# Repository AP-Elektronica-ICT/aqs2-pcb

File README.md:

# Schema airsensor

# Schema LoRaWAN

# Schema HIH8xxx

# Schema JTAG
<<<<<<< HEAD

=======

>>>>>>> c74764702c0ad45f76e91693a2fbca707ce8f4d9

# PCB airsensor

# PCB LoRaWAN

# PCB HIH8xxx

# PCB JTAG
<<<<<<< HEAD

=======

>>>>>>> c74764702c0ad45f76e91693a2fbca707ce8f4d9

# 3D airsensor

# 3D LoRaWAN

# 3D HIH8xxx

# 3D JTAG
<<<<<<< HEAD

=======

>>>>>>> c74764702c0ad45f76e91693a2fbca707ce8f4d9

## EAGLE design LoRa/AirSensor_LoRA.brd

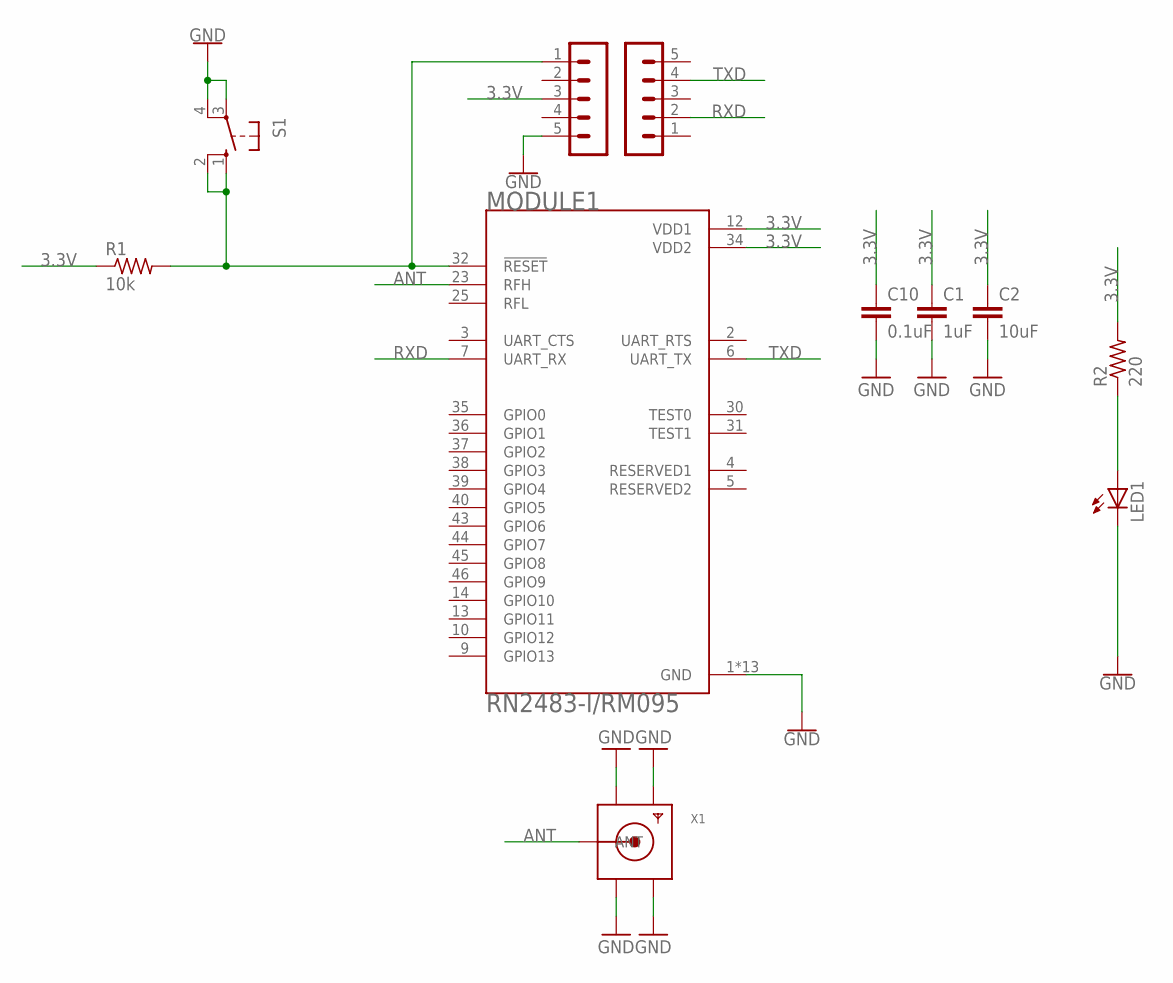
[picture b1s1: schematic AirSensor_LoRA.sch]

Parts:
C1: 1uF; 0805
C2: 10uF; 0805
C10: 0.1uF; 0805
LED1: LEDCHIPLED_0805; CHIPLED_0805
MODULE1: RN2483-I/RM095; MICROCHIP_RN2483-I/RM095
R1: 10k; RES_0805
R2: 220; RES_0805
RFM95W_1: LoRa_1; MA05-1
RFM95W_2: LoRa_2; MA05-1
S1: 10-XX; B3F-10XX
X1: SMACONNECTOR_EDGE; SMA_EDGELAUNCH

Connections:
3.3V: C1.1, C2.1, C10.1, MODULE1.12 (VDD1), MODULE1.34 (VDD2), R1.1, R2.2, RFM95W_1.3
ANT: MODULE1.23 (RFH), X1.P (ANT)
GND: C1.2, C2.2, C10.2, LED1.C, MODULE1.1 (GND), MODULE1.8 (GND), MODULE1.11 (GND), MODULE1.20 (GND), MODULE1.21 (GND), MODULE1.22 (GND), MODULE1.24 (GND), MODULE1.26 (GND), MODULE1.27 (GND), MODULE1.28 (GND), MODULE1.33 (GND), MODULE1.41 (GND), MODULE1.47 (GND), RFM95W_1.5, S1.3, S1.4 (P1), X1.GND@1 (GND4), X1.GND@2 (GND3), X1.GND@3 (GND2), X1.GND@4 (GND1)
unnamed: LED1.A, R2.1
unnamed: MODULE1.32 (!RESET), R1.2, RFM95W_1.1, S1.1 (S), S1.2 (S1)
RXD: MODULE1.7 (UART_RX), RFM95W_2.2
TXD: MODULE1.6 (UART_TX), RFM95W_2.4

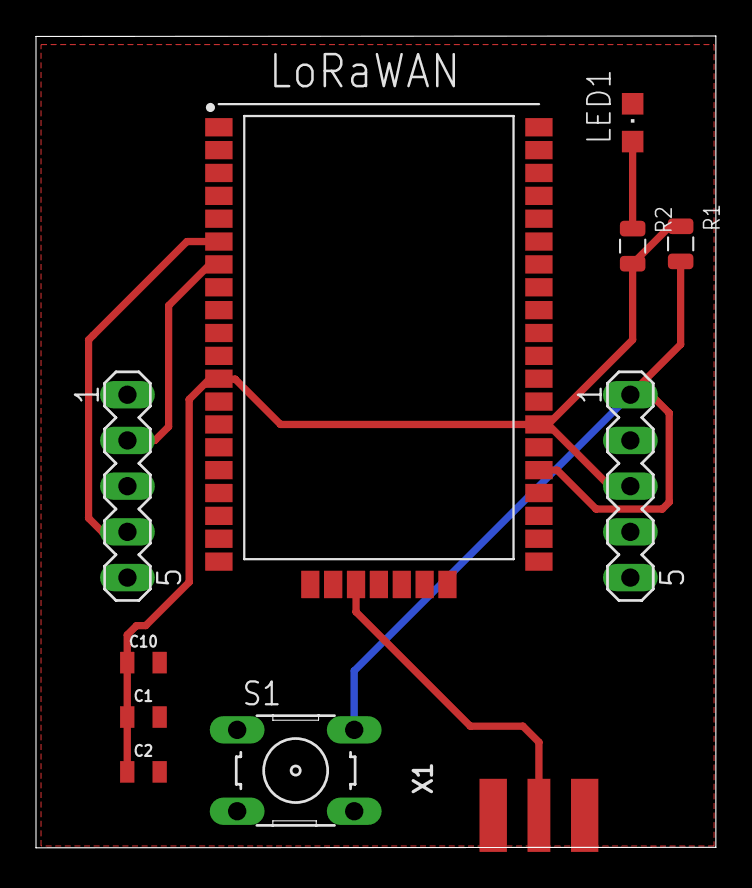
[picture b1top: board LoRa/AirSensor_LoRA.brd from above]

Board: 2 copper layers, 37.8 x 45.1 mm, 11 parts (0 on the bottom side), 7 nets.

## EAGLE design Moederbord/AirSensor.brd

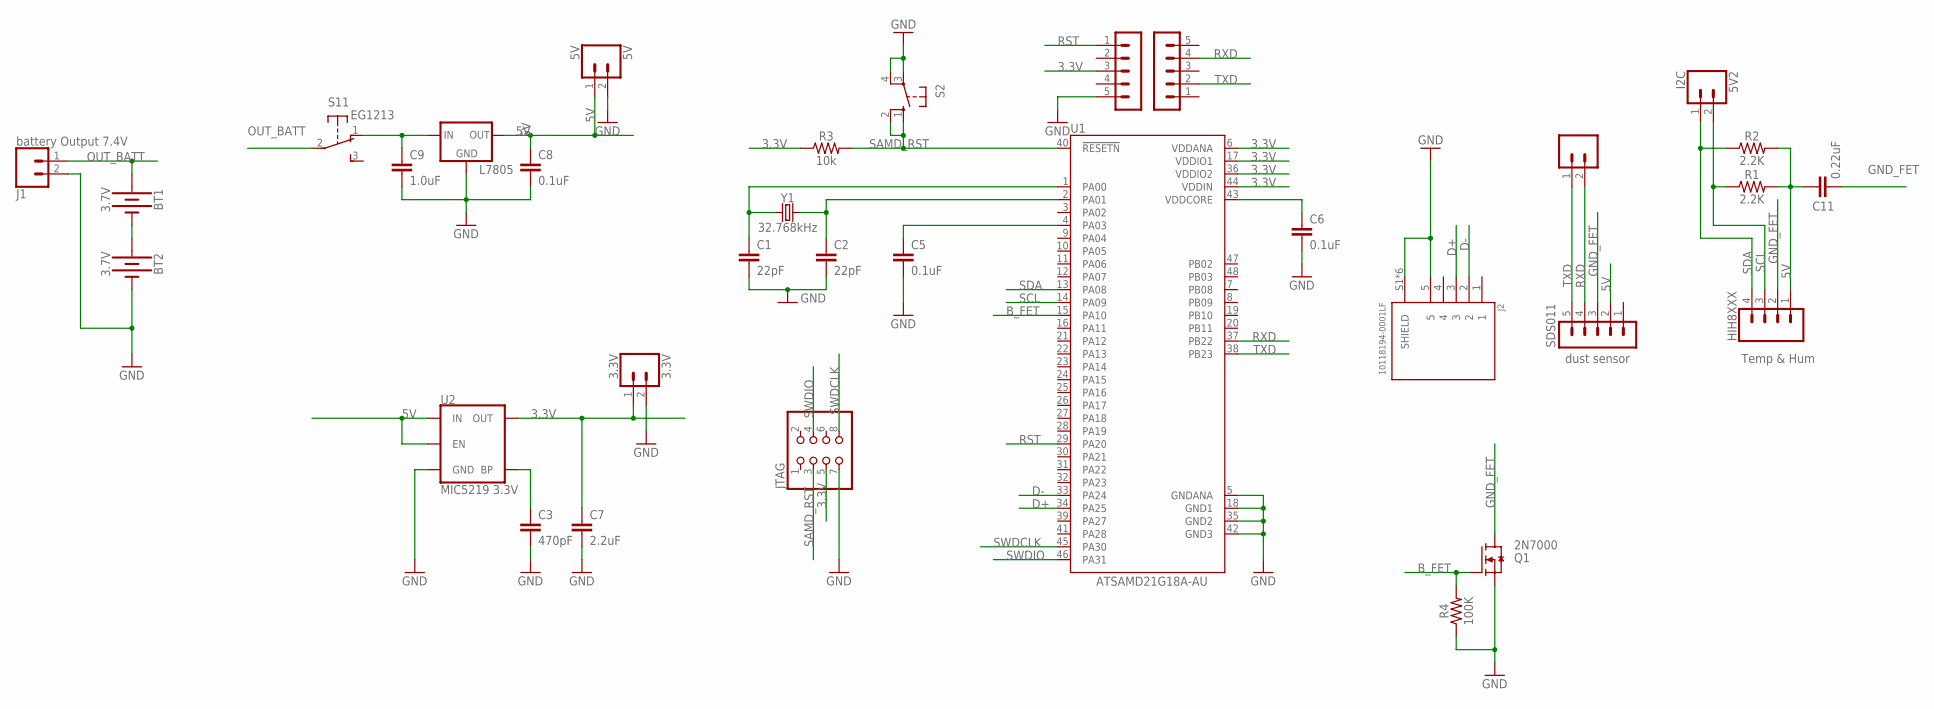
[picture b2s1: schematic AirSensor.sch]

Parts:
3.3V: 3.3V; 1X02
5V: 5V; 1X02
5V1: UART; 1X02
5V2: I2C; 1X02
BT1, BT2: 3.7V; BATTERY_18650-HOLDER
C1, C2: 22pF; 0805
C3: 470pF; 0805
C5, C6, C8: 0.1uF; 0805
C7: 2.2uF; 0805
C9: 1.0uF; 0805
C11: 0.22uF; 0805
HIH8XXX: Temp & Hum; 1X04
J1: battery Output 7.4V; 1X02
J2: 10118194-0001LF; AMPHENOL_10118194-0001LF
JTAG: PINHD-2X4; 2X04
L7805: V_REG_78XXSINK; TO220-IGO
Q1: 2N7000; TO92
R1, R2: 2.2K; 0805
R3: 10k; 0805
R4: 100K; 0805
RN2483: LoRa1; MA05-1
RN2483_2: LoRa_2; MA05-1
S1: EG1213
S2: 10-XX; B3F-10XX
SDS011: dust sensor; MA05-1
U1: ATSAMD21G18A-AU; QFP50P900X900X120-48N
U2: MIC5219 3.3V; SOT23-5
Y1: 32.768kHz; CRYSTAL-SMD-3.2X1.5MM

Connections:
3.3V: 3.3V.1, C7.1, JTAG.5, R3.1, RN2483.3, U1.6 (VDDANA), U1.17 (VDDIO1), U1.36 (VDDIO2), U1.44 (VDDIN), U2.5 (OUT)
5V: 5V.1, C8.1, C11.1, HIH8XXX.1, L7805.OUT, R1.2, R2.2, SDS011.2, U2.1 (IN), U2.3 (EN)
B_FET: Q1.2 (G), R4.2, U1.15 (PA10)
D+: J2.3, U1.34 (PA25)
D-: J2.2, U1.33 (PA24)
GND: 3.3V.2, 5V.2, BT2.GND@1 (-), C1.2, C2.2, C3.2, C5.2, C6.2, C7.2, C8.2, C9.2, J1.2, J2.5, J2.S1 (SHIELD), J2.S2 (SHIELD), J2.S3 (SHIELD), J2.S4 (SHIELD), J2.S5 (SHIELD), J2.S6 (SHIELD), JTAG.7, L7805.GND, Q1.1 (S), R4.1, RN2483.5, S2.3, S2.4 (P1), U1.5 (GNDANA), U1.18 (GND1), U1.35 (GND2), U1.42 (GND3), U2.2 (GND)
GND_FET: C11.2, HIH8XXX.2, Q1.3 (D), SDS011.3
unnamed: C5.1, U1.4 (PA03)
unnamed: C6.1, U1.43 (VDDCORE)
unnamed: C1.1, U1.1 (PA00), Y1.P$1 (1)
unnamed: C3.1, U2.4 (BP)
unnamed: BT1.GND@1 (-), BT2.PWR@1 (+)
unnamed: C2.1, U1.2 (PA01), Y1.P$2 (2)
OUT_BATT: BT1.PWR@1 (+), C9.1, J1.1, L7805.IN, S1.1 (O), S1.2
RST: RN2483.1, U1.29 (PA20)
RXD: 5V1.2, RN2483_2.4, SDS011.4, U1.37 (PB22)
SAMD_RST: JTAG.3, R3.2, S2.1 (S), S2.2 (S1), U1.40 (!RESETN)
SCL: 5V2.2, HIH8XXX.3, R1.1, U1.14 (PA09)
SDA: 5V2.1, HIH8XXX.4, R2.1, U1.13 (PA08)
SWDCLK: JTAG.8, U1.45 (PA30)
SWDIO: JTAG.4, U1.46 (PA31)
TXD: 5V1.1, RN2483_2.2, SDS011.5, U1.38 (PB23)

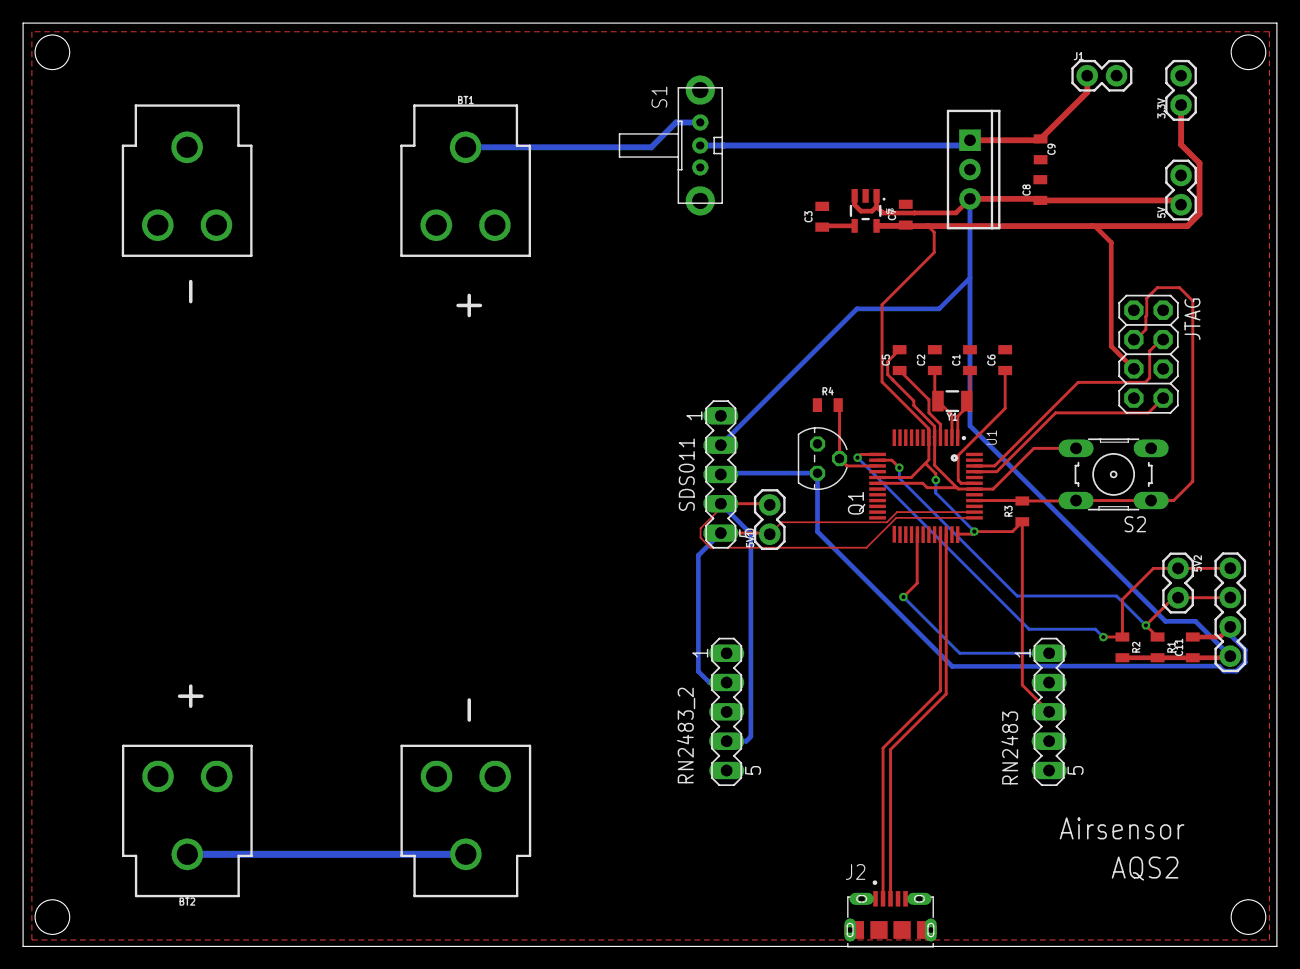
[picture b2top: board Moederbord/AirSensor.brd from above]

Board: 2 copper layers, 108.6 x 80.0 mm, 33 parts (0 on the bottom side), 22 nets.

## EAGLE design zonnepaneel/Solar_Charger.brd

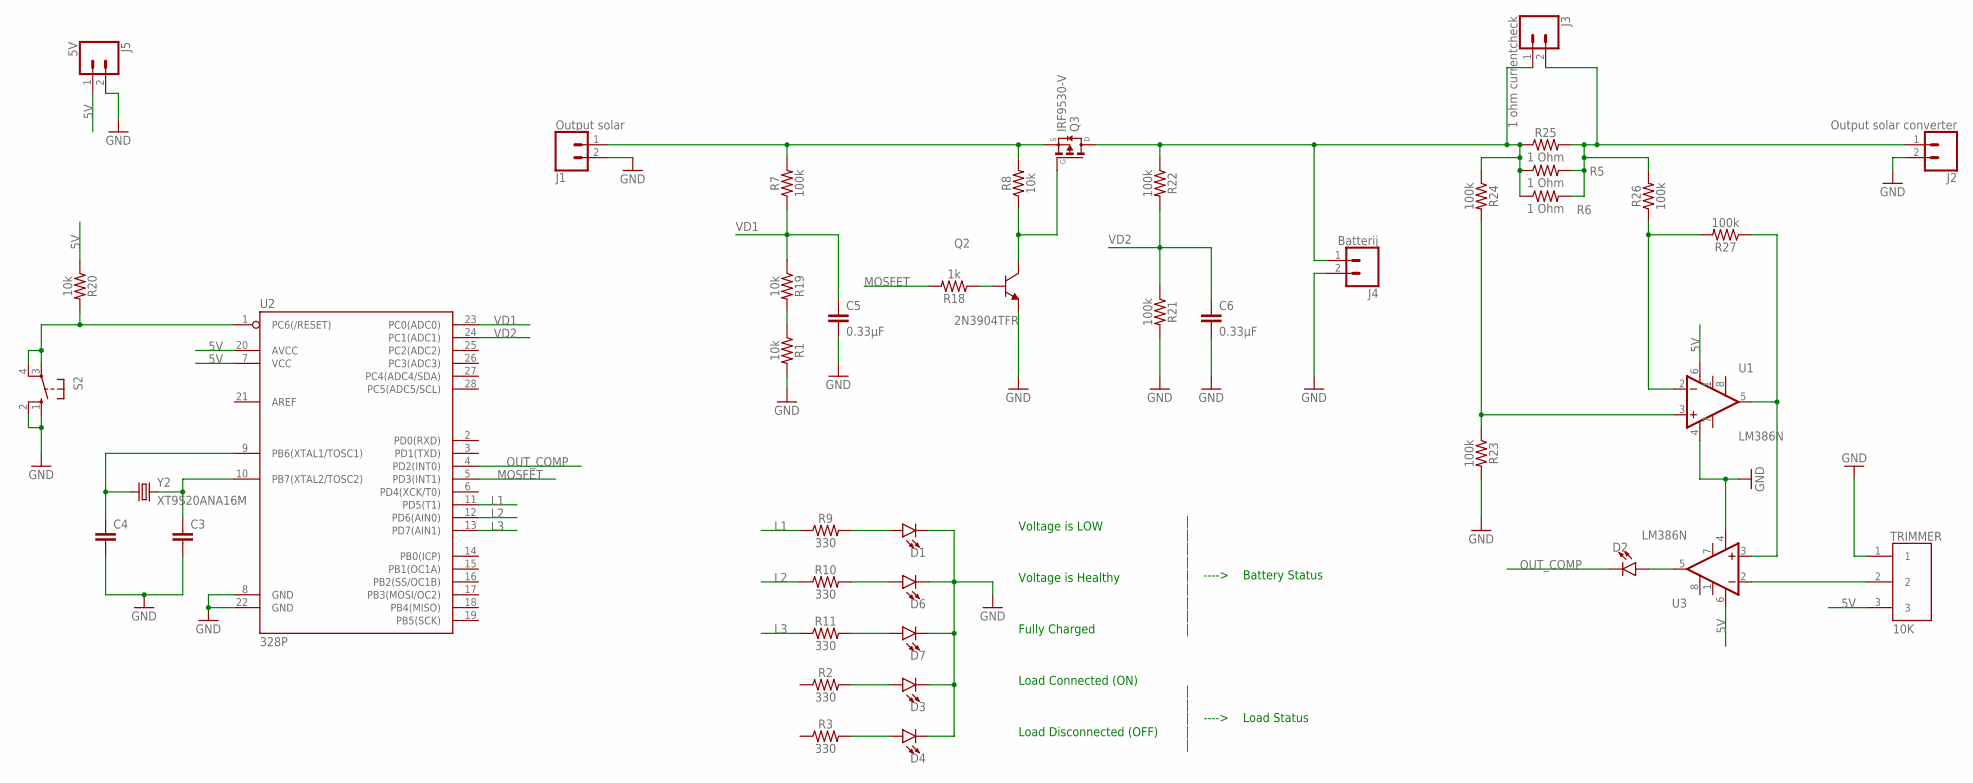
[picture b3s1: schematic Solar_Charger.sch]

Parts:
C3, C4: C2.5/5; C2.5-5
C5, C6: 0.33µF; C2.5-5
D1, D2, D3, D4, D6, D7: LED-3MM-NO_SILK; LED_3MM-NS
J1: Output solar; 1X02
J2: Output solar converter; 1X02
J3: 1 ohm currentcheck; 1X02
J4: Batterij; 1X02
J5: 5V; 1X02
Q2: 2N3904TFR; TO92254P520H877-3
Q3: IRF9530-V; TO220V
R1, R8, R19, R20: 10k; AXIAL-0.3
R2, R3, R9, R10, R11: 330; AXIAL-0.3
R5, R6, R25: 1 Ohm; AXIAL-0.3
R7, R21, R22, R23, R24, R26, R27: 100k; AXIAL-0.3
R18: 1k; AXIAL-0.3
S2: 10-XX; B3F-10XX
TRIMMER: 10K; TRIM_404806347006
U1, U3: LM386N; DIP08
U2: 328P; DIP28
Y2: XT9S20ANA16M; XTAL_XT9S20ANA16M

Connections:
5V: J5.1, R20.P$1 (1), TRIMMER.3, U1.6 (V+), U2.7 (VCC), U2.20 (AVCC), U3.6 (V+)
GND: C3.2, C4.2, C5.2, C6.2, D1.K (C), D3.K (C), D4.K (C), D6.K (C), D7.K (C), J1.2, J2.2, J4.2, J5.2, Q2.1 (E), R1.P$2 (2), R21.P$2 (2), R23.P$2 (2), S2.1 (S), S2.2 (S1), TRIMMER.1, U1.4 (V-), U2.8 (GND), U2.22 (GND), U3.4 (V-)
GND1: R20.P$2 (2), S2.3, S2.4 (P1), U2.1 (PC6(/RESET))
L1: R9.P$1 (1), U2.11 (PD5(T1))
L2: R10.P$1 (1), U2.12 (PD6(AIN0))
L3: R11.P$1 (1), U2.13 (PD7(AIN1))
MOSFET: R18.P$2 (2), U2.5 (PD3(INT1))
unnamed: J1.1, Q3.3 (S), R7.P$2 (2), R8.P$2 (2)
unnamed: D3.A, R2.P$2 (2)
unnamed: D4.A, R3.P$2 (2)
unnamed: R23.P$1 (1), R24.P$2 (2), U1.3 (+IN)
unnamed: R26.P$1 (1), R27.P$2 (2), U1.2 (-IN)
unnamed: R1.P$1 (1), R19.P$2 (2)
unnamed: C4.1, U2.9 (PB6(XTAL1/TOSC1)), Y2.1
unnamed: C3.1, U2.10 (PB7(XTAL2/TOSC2)), Y2.2
unnamed: Q2.2 (B), R18.P$1 (1)
unnamed: Q2.3 (C), Q3.1 (G), R8.P$1 (1)
unnamed: J3.1, J4.1, Q3.2 (D), R5.P$1 (1), R6.P$1 (1), R22.P$1 (1), R24.P$1 (1), R25.P$1 (1)
unnamed: R27.P$1 (1), U1.5 (OUT), U3.3 (+IN)
unnamed: TRIMMER.2, U3.2 (-IN)
unnamed: D2.A, U3.5 (OUT)
unnamed: J2.1, J3.2, R5.P$2 (2), R6.P$2 (2), R25.P$2 (2), R26.P$2 (2)
unnamed: D1.A, R9.P$2 (2)
unnamed: D6.A, R10.P$2 (2)
unnamed: D7.A, R11.P$2 (2)
OUT_COMP: D2.K (C), U2.4 (PD2(INT0))
VD1: C5.1, R7.P$1 (1), R19.P$1 (1), U2.23 (PC0(ADC0))
VD2: C6.1, R21.P$1 (1), R22.P$2 (2), U2.24 (PC1(ADC1))

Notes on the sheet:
Voltage is LOW
Voltage is Healthy
Fully Charged
Load Connected (ON)
Load Disconnected (OFF)
| | | | | ----> Battery Status | | | |
| | | ----> Load Status | |

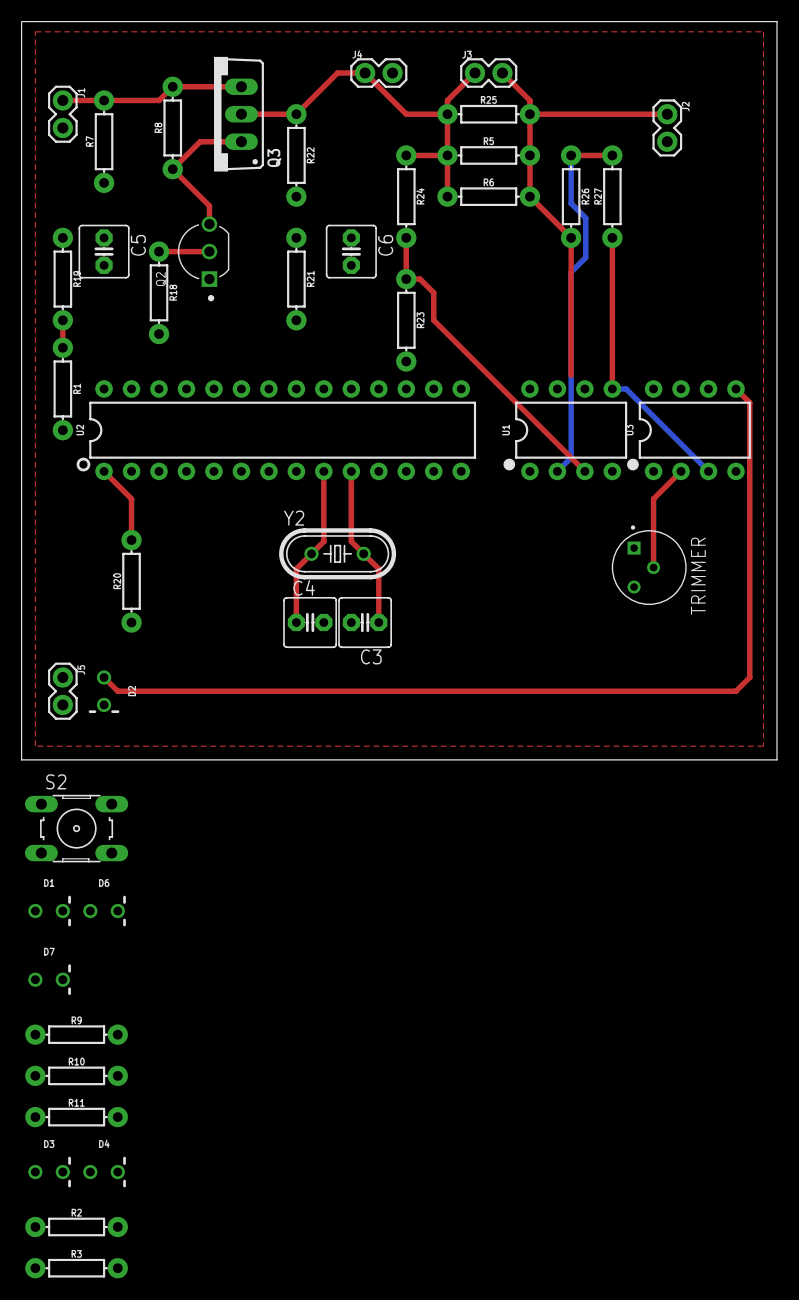
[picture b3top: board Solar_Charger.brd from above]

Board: 2 copper layers, 69.8 x 68.2 mm, 43 parts (0 on the bottom side), 28 nets.

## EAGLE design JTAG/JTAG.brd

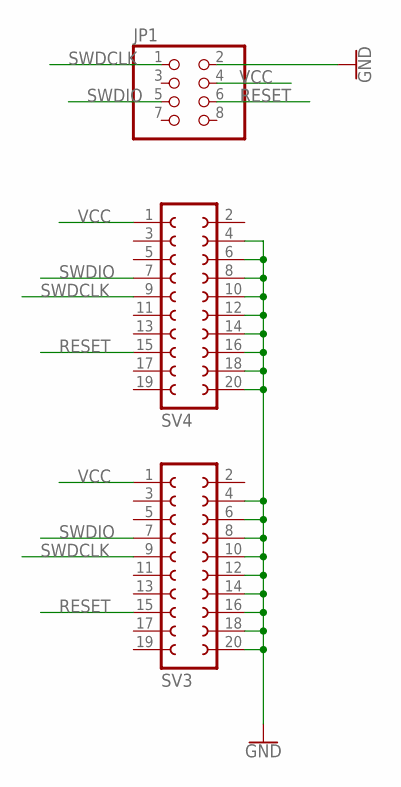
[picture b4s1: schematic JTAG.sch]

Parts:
JP1: PINHD-2X4; 2X04
SV3, SV4: FE10-2

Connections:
GND: JP1.2, SV3.4, SV3.6, SV3.8, SV3.10, SV3.12, SV3.14, SV3.16, SV3.18, SV3.20, SV4.4, SV4.6, SV4.8, SV4.10, SV4.12, SV4.14, SV4.16, SV4.18, SV4.20
RESET: JP1.6, SV3.15, SV4.15
SWDCLK: JP1.1, SV3.9, SV4.9
SWDIO: JP1.5, SV3.7, SV4.7
VCC: JP1.4, SV3.1, SV4.1

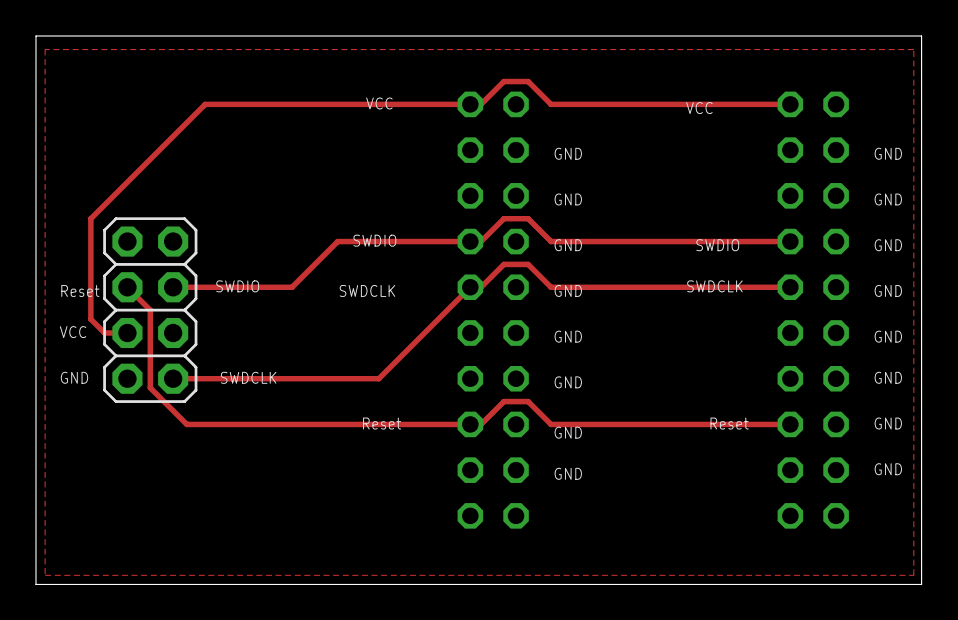
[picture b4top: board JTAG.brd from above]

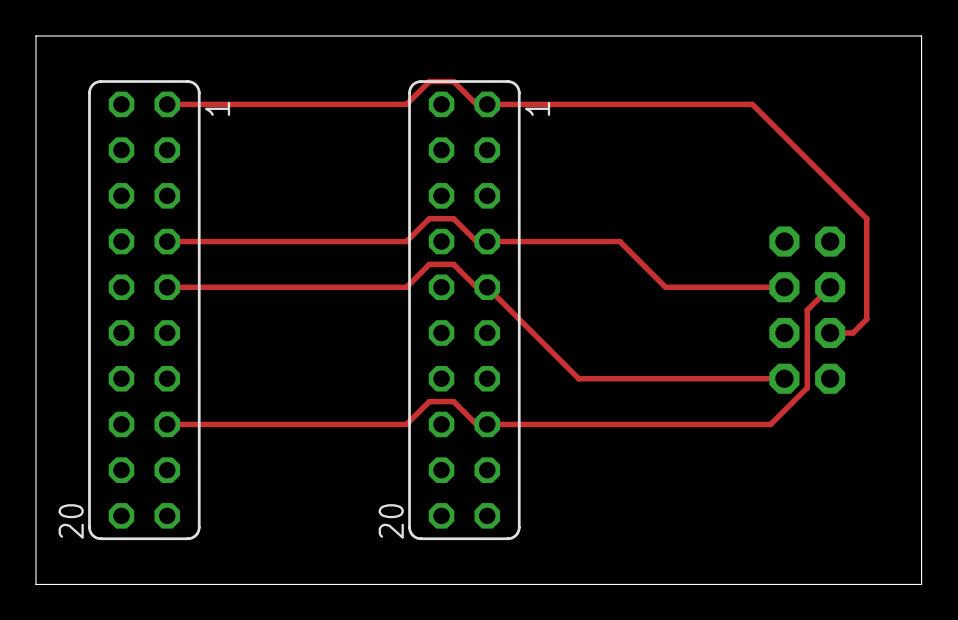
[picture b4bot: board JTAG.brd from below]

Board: 2 copper layers, 49.2 x 30.5 mm, 3 parts (2 on the bottom side), 5 nets.

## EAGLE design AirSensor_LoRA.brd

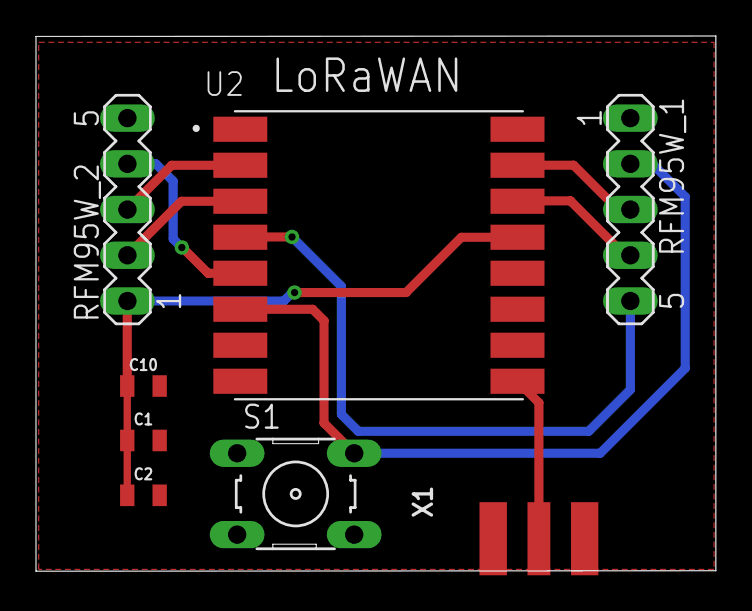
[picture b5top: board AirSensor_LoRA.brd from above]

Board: 2 copper layers, 37.8 x 29.7 mm, 8 parts (0 on the bottom side), 11 nets.

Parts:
C1: 1uF; 0805
C2: 10uF; 0805
C10: 0.1uF; 0805
RFM95W_1: LoRa_1; MA05-1
RFM95W_2: LoRa_2; MA05-1
S1: B3F-10XX
U2: RFM95W-915S2; XCVR_RFM95W-915S2
X1: SMA_EDGELAUNCH

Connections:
3.3V: S1.3, S1.4
GND: C1.2, C2.2, C10.2, RFM95W_2.5, U2.1, U2.8, U2.10, X1.GND@1, X1.GND@2, X1.GND@3, X1.GND@4
unnamed: RFM95W_1.2, S1.1, S1.2, U2.6
unnamed: C1.1, C2.1, C10.1, RFM95W_2.1, U2.13
unnamed: RFM95W_2.2, U2.3
unnamed: RFM95W_2.3, U2.2
unnamed: RFM95W_2.4, U2.5
unnamed: RFM95W_1.5, U2.4
unnamed: RFM95W_1.4, U2.14
unnamed: RFM95W_1.3, U2.15
unnamed: U2.9, X1.P

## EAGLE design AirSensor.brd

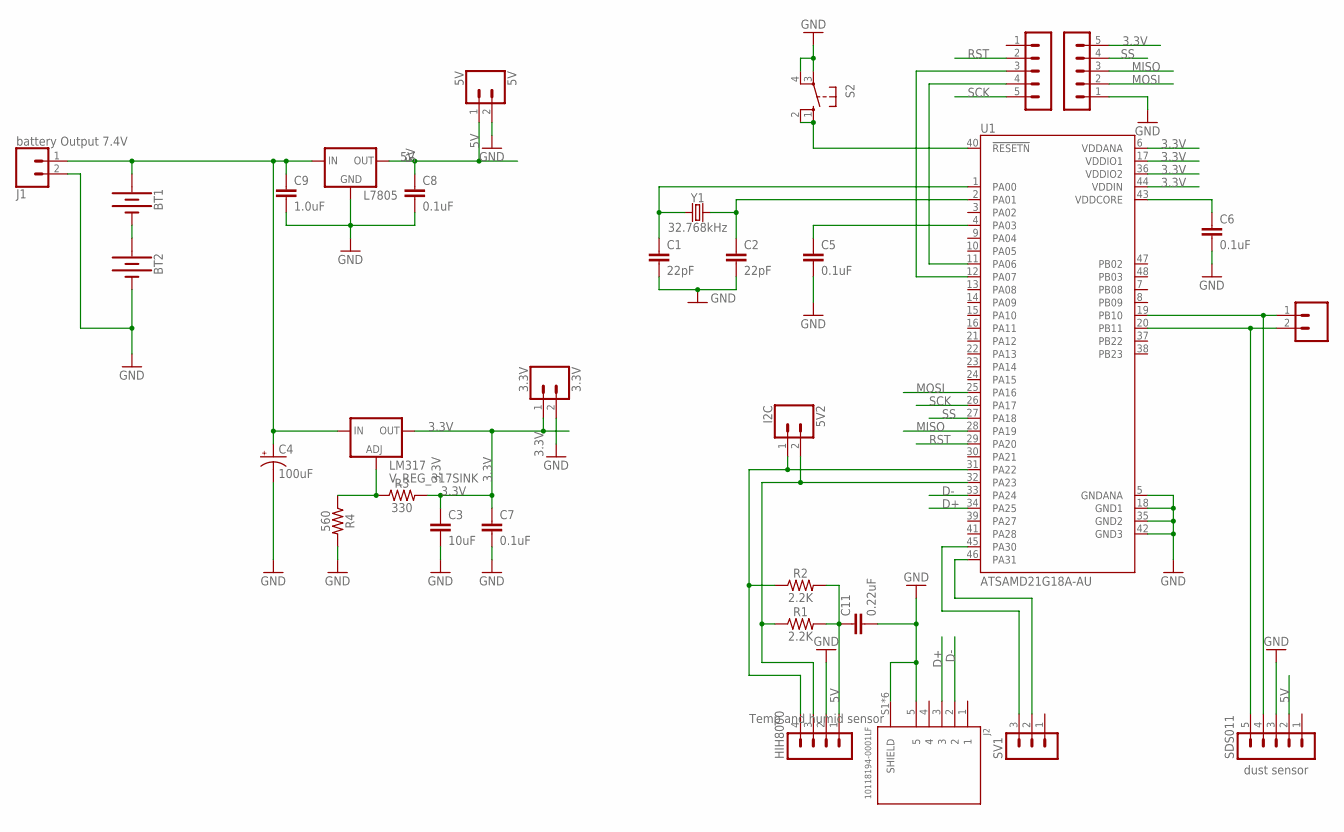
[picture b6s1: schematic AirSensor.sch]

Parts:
3.3V: 3.3V; 1X02
5V: 5V; 1X02
5V1: UART; 1X02
5V2: I2C; 1X02
BT1, BT2: BATTERY-18650; BATTERY_18650-HOLDER
C1, C2: 22pF; 0805
C3: 10uF; 0805
C4: 100uF; CPOL-RADIAL-2.5MM-6.5MM
C5, C6, C7, C8: 0.1uF; 0805
C9: 1.0uF; 0805
C11: 0.22uF; 0805
HIH8000: Temp and humid sensor; MA04-1
J1: battery Output 7.4V; 1X02
J2: 10118194-0001LF; AMPHENOL_10118194-0001LF
L7805: V_REG_78XXSINK; TO220-IGO
LM317: V_REG_317SINK; TO220-ADJ
R1, R2: 2.2K; 0805
R3: 330; 0805
R4: 560; 0805
RFM95W: LoRa1; MA05-1
RFM95W_2: LoRa_2; MA05-1
S2: 10-XX; B3F-10XX
SDS011: dust sensor; MA05-1
SV1: MA03-1
U1: ATSAMD21G18A-AU; QFP50P900X900X120-48N
Y1: 32.768kHz; CRYSTAL-SMD-3.2X1.5MM

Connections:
3.3V: 3.3V.1, C3.1, C7.1, LM317.OUT, R3.2, RFM95W_2.5, U1.6 (VDDANA), U1.17 (VDDIO1), U1.36 (VDDIO2), U1.44 (VDDIN)
5V: 5V.1, C8.1, C11.1, HIH8000.1, L7805.OUT, R1.2, R2.2, SDS011.2
D+: J2.3, U1.34 (PA25)
D-: J2.2, U1.33 (PA24)
GND: 3.3V.2, 5V.2, BT2.GND@1 (-), C1.2, C2.2, C3.2, C4.2 (-), C5.2, C6.2, C7.2, C8.2, C9.2, C11.2, HIH8000.2, J1.2, J2.5, J2.S1 (SHIELD), J2.S2 (SHIELD), J2.S3 (SHIELD), J2.S4 (SHIELD), J2.S5 (SHIELD), J2.S6 (SHIELD), L7805.GND, R4.2, RFM95W_2.1, S2.3, S2.4 (P1), SDS011.3, U1.5 (GNDANA), U1.18 (GND1), U1.35 (GND2), U1.42 (GND3)
MISO: RFM95W_2.3, U1.28 (PA19)
MOSI: RFM95W_2.2, U1.25 (PA16)
unnamed: 5V2.2, HIH8000.3, R1.1, U1.32 (PA23)
unnamed: 5V1.1, SDS011.4, U1.19 (PB10)
unnamed: 5V1.2, SDS011.5, U1.20 (PB11)
unnamed: C5.1, U1.4 (PA03)
unnamed: C6.1, U1.43 (VDDCORE)
unnamed: C1.1, U1.1 (PA00), Y1.P$1 (1)
unnamed: LM317.ADJ, R3.1, R4.1
unnamed: BT1.GND@1 (-), BT2.PWR@1 (+)
unnamed: C2.1, U1.2 (PA01), Y1.P$2 (2)
unnamed: S2.1 (S), S2.2 (S1), U1.40 (!RESETN)
unnamed: BT1.PWR@1 (+), C4.1 (+), C9.1, J1.1, L7805.IN, LM317.IN
unnamed: 5V2.1, HIH8000.4, R2.1, U1.31 (PA22)
unnamed: RFM95W.4, U1.11 (PA06)
unnamed: SV1.3, U1.45 (PA30)
unnamed: SV1.2, U1.46 (PA31)
unnamed: RFM95W.3, U1.12 (PA07)
RST: RFM95W.2, U1.29 (PA20)
SCK: RFM95W.5, U1.26 (PA17)
SS: RFM95W_2.4, U1.27 (PA18)

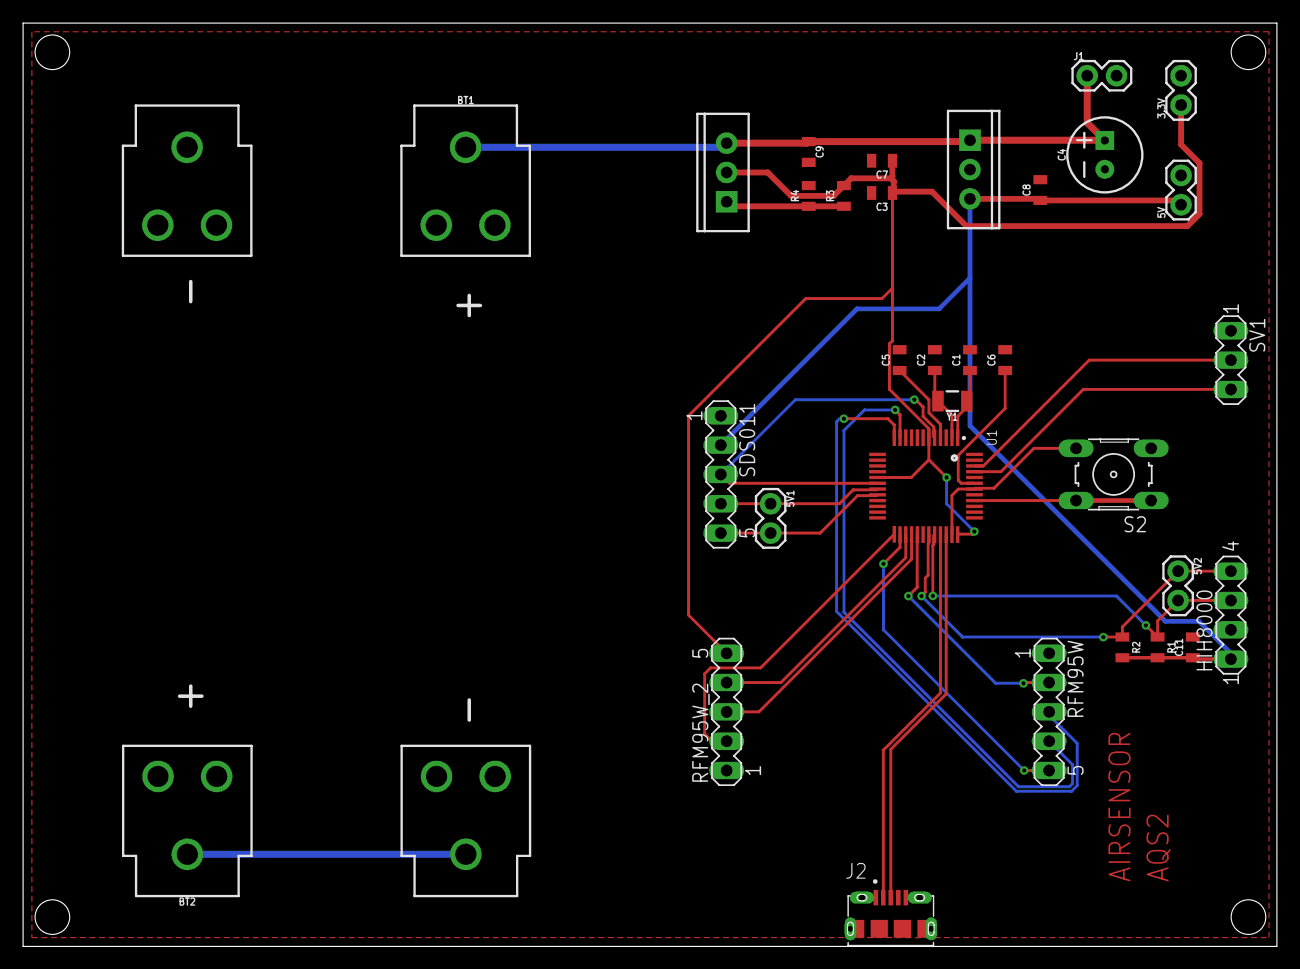
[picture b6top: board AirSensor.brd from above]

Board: 2 copper layers, 108.6 x 80.0 mm, 32 parts (0 on the bottom side), 26 nets.

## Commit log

2020-10-04 Added schema of sensors and SAMD21G
2020-10-16 added all 3 schematics en all 3 PCB deigns
2020-10-21 added JTAG schematic and PCB + all pictures
2020-10-21 added pictures of schematic, PCB and 3D model to read.me file
2020-10-22 updated JTAG schematic PCB and 3D model
2020-10-22 fixed JTAG name
2020-10-26 added Gerber files in map
2020-11-03 box en deksel in 3d tekening gemaakt
2020-12-09 nieuw schema lora bordje
2020-12-11 feedback verwerking
2020-12-11 temp commit
2020-12-11 added gerber files
2020-12-14 fixed some bugs
2020-12-14 stl en gcode files toegevoegd
2021-01-26 save files verwijderd
2021-01-28 added solar charger, PCB image, ...
2021-02-02 rx/tx fout opgelost in PCB

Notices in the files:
parts and their libraries:
SparkFun-Connectors: Licensing: Creative Commons ShareAlike 4.0 International - https://creativecommons.org/licenses/by-sa/4.0
SparkFun-Aesthetics: Licensing: CC v3.0 Share-Alike You are welcome to use this library for commercial purposes.
